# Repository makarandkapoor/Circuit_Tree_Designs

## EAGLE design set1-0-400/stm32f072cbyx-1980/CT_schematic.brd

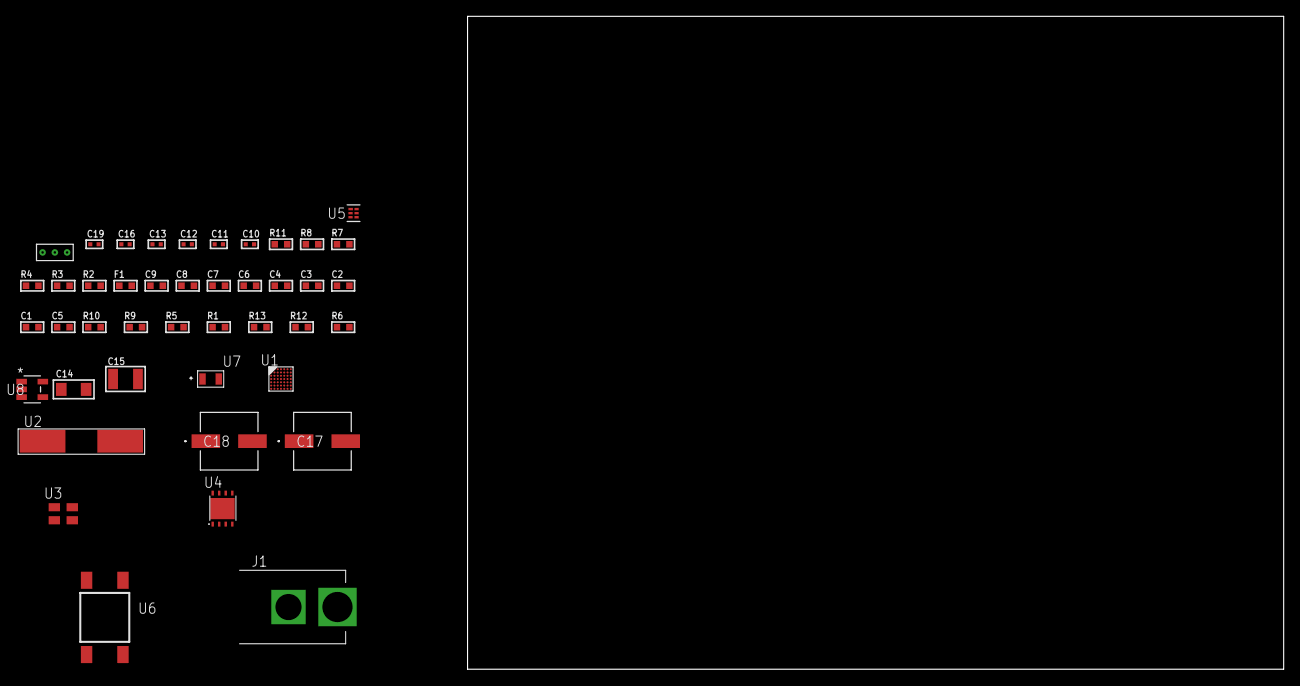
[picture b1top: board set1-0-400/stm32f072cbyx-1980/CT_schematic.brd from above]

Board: 2 copper layers, 100.0 x 80.0 mm, 43 parts (0 on the bottom side), 20 nets, no tracks yet.

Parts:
C1, C9: 1e-06; C0603
C2, C3, C4, C6, C7: 1e-07; C0603
C5: 4.7e-06; C0603
C8: 1e-08; C0603
C10, C11: 1e-11; C0402
C12, C13, C19: 1e-08; C0402
C14: 1e-05; C1206
C15: 1e-05; C1210
C16: 1e-07; C0402
C17, C18: 0.0001; EXV-9H
F1: 240.0; L0603
J1: PJ-037B; PJ-037B_PACKAGE
R1, R5, R9, R10: 10000.0; R0603
R2, R8: 1000.0; R0603
R3: 1600.5; R0603
R4: 4700.0; R0603
R6: 100000.0; R0603
R7: 2231.0; R0603
R11: 9100.0; R0603
R12: 680000.0; R0603
R13: 120000.0; R0603
U1: stm32f072cby6; WLCSP49
U2: ABLS-25.000MHZ-B2F-T
U3: ASEK-32.768KHz-ECST; ASEK
U4: LP3878SDX-ADJ/NOPB; WSON-8
U5: TPS3895ADRYR; SON-6
U6: 4-1437565-2; SW_4-1437565-2
U7: Q65110A2395; LGM67K-G1J2-24-Z
U8: nc7sz125m5x; NC7SZ125M5X
U9: Dummy; DUMMY_PACKAGE_86

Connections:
CLK_CRYSTAL_U1_D6: C10.1, U1.D6, U2.1
CLK_CRYSTAL_U1_D7: C11.1, U1.D7, U2.2
CLK_U1_C7: U1.C7, U3.3
GND: C1.2, C2.2, C3.2, C4.2, C5.2, C6.2, C7.2, C8.2, C9.2, C10.2, C11.2, C12.2, C13.2, C14.2, C15.2, C16.2, C17.2, C18.2, C19.2, J1.2, R2.2, R5.2, R8.2, R11.2, R13.2, U1.A6, U1.B1, U1.D3, U1.E6, U3.2, U4.3, U4.PAD, U5.2, U7.C, U8.1, U8.3, U9.1
NET_U1_A5: R5.1, U1.A5
NET_U1_E7: R4.1, U1.E7, U8.4
NET_U1_F7: C8.1, C9.1, F1.1, U1.F7
NET_U1_G6: R3.1, U1.G6, U7.A
NET_U1_G7: R1.1, U1.G7, U6.3, U6.4
NET_U4_1: C13.1, U4.1
NET_U4_6: R7.2, R8.1, U4.6
NET_U4_8: R6.1, U4.8
NET_U5_1: R10.1, R11.1, U5.1
NET_U5_3: R12.2, R13.1, U5.3
NET_U5_4: R9.1, U5.4, U8.2
NET_U6_1: R2.1, U6.1, U6.2
PROC_TIM1_CH2: U1.D2, U9.2
PROC_TIM1_CH4: U1.C1, U9.3
VCC_S1_8V5: C14.1, C17.1, C18.1, J1.1, R6.2, U4.4
VCC_TIER1_3V3: C1.1, C2.1, C3.1, C4.1, C5.1, C6.1, C7.1, C12.1, C15.1, C16.1, C19.1, F1.2, R1.2, R3.2, R4.2, R7.1, R9.2, R10.2, R12.1, U1.A7, U1.B2, U1.B7, U1.F2, U3.4, U4.5, U5.6, U8.5

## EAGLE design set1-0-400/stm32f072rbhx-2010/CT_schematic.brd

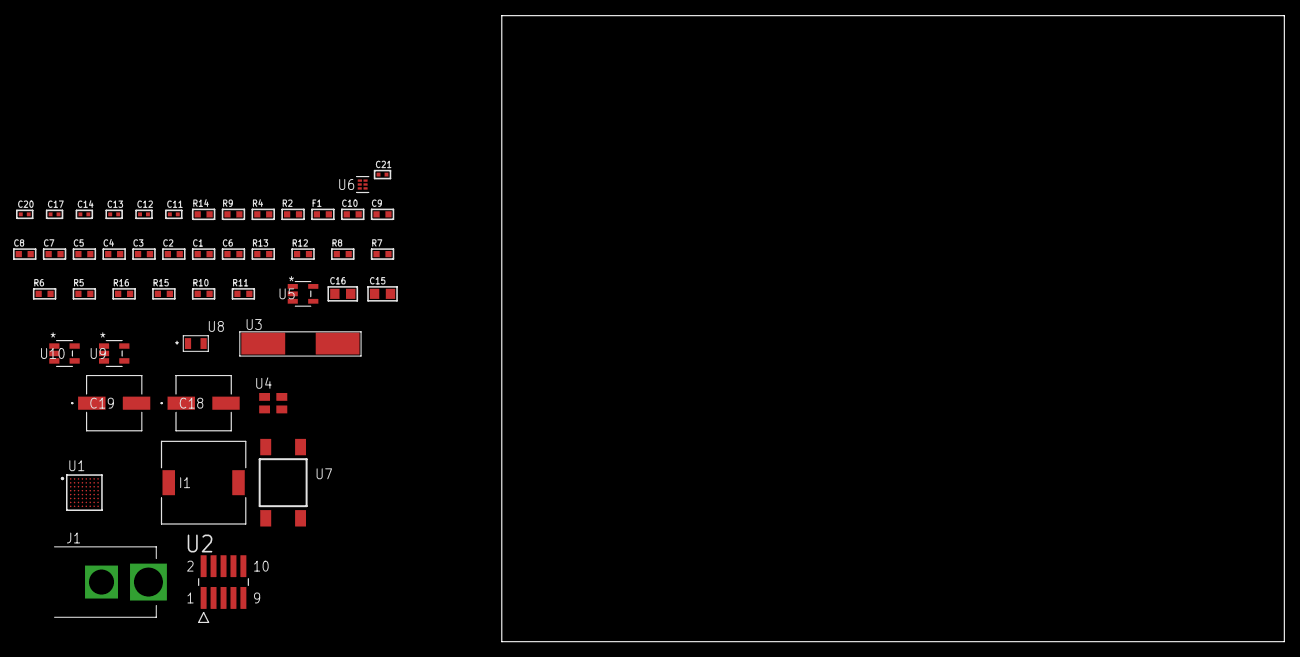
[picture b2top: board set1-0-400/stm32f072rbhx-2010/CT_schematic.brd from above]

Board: 2 copper layers, 100.0 x 80.0 mm, 48 parts (0 on the bottom side), 21 nets, no tracks yet.

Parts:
C1, C10: 1e-06; C0603
C2, C3, C4, C5, C7, C8: 1e-07; C0603
C6: 4.7e-06; C0603
C9: 1e-08; C0603
C11, C12: 1e-11; C0402
C13, C17: 1e-07; C0402
C14, C20, C21: 1e-08; C0402
C15, C16: 1e-05; C0805
C18, C19: 0.0001; EXV-9H
F1: 240.0; L0603
I1: 7e-06; DR1040
J1: PJ-037B; PJ-037B_PACKAGE
R2: 1000.0; R0603
R4: 4700.0; R0603
R5, R6, R7, R8, R12, R13: 10000.0; R0603
R9: 5.0; R0603
R10: 220000.0; R0603
R11: 1000000.0; R0603
R14: 9100.0; R0603
R15: 680000.0; R0603
R16: 120000.0; R0603
U1: stm32f072rbh7; UFBGA64
U2: FTSH-105-01-L-DV-K; SAMTEC_FTSH-105-01-L-DV-K
U3: ABLS-25.000MHZ-B2F-T
U4: ASEK-32.768KHz-ECST; ASEK
U5: ltc3406es5; TSOT-23-5
U6: TPS3895ADRYR; SON-6
U7: 4-1437565-2; SW_4-1437565-2
U8: Q65110A2395; LGM67K-G1J2-24-Z
U9, U10: nc7sz125m5x; NC7SZ125M5X

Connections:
CLK_CRYSTAL_U1_C1: C11.1, U1.C1, U3.1
CLK_CRYSTAL_U1_D1: C12.1, U1.D1, U3.2
CLK_U1_A1: U1.A1, U4.3
GND: C1.2, C2.2, C3.2, C4.2, C5.2, C6.2, C7.2, C8.2, C9.2, C10.2, C11.2, C12.2, C13.2, C14.2, C15.2, C16.1, C16.2, C17.2, C18.2, C19.2, C20.2, C21.2, J1.2, R2.2, R5.2, R9.2, R10.2, R14.2, R16.2, U1.C2, U1.D4, U1.D5, U1.D6, U1.F1, U2.3, U2.5, U4.2, U5.2, U6.2, U8.C, U9.2, U9.3, U10.1, U10.3
NET_U1_B4: R5.1, U1.B4
NET_U1_E1: R4.1, U1.E1, U10.4
NET_U1_H1: C9.1, C10.1, F1.1, U1.H1
NET_U1_H8: U7.3, U7.4
NET_U2_9: R9.1, U2.9
NET_U5_3: I1.1, U5.3
NET_U5_5: R10.1, R11.1, U5.5
NET_U5_ATNET_3: I1.2, R11.2
NET_U6_1: R13.1, R14.1, U6.1
NET_U6_3: R15.2, R16.1, U6.3
NET_U6_4: R12.1, U6.4, U9.4, U10.2
NET_U7_1: R2.1, U7.1, U7.2
PROC_SYS_SWCLK: R7.1, U1.A7, U2.4
PROC_SYS_SWDIO: R8.1, U1.A8, U2.2
RST_OUT_U2_JTAG_RST_B: R6.1, U2.10, U9.1
VCC_S1_4V8: C15.1, C18.1, C19.1, J1.1, U5.4
VCC_TIER1_3V3: C1.1, C2.1, C3.1, C4.1, C5.1, C6.1, C7.1, C8.1, C13.1, C14.1, C16.2, C17.1, C20.1, C21.1, F1.2, I1.2, R4.2, R6.2, R7.2, R8.2, R11.2, R12.2, R13.2, R15.1, U1.B2, U1.D2, U1.E4, U1.E5, U1.E6, U2.1, U4.4, U6.6, U9.5, U10.5

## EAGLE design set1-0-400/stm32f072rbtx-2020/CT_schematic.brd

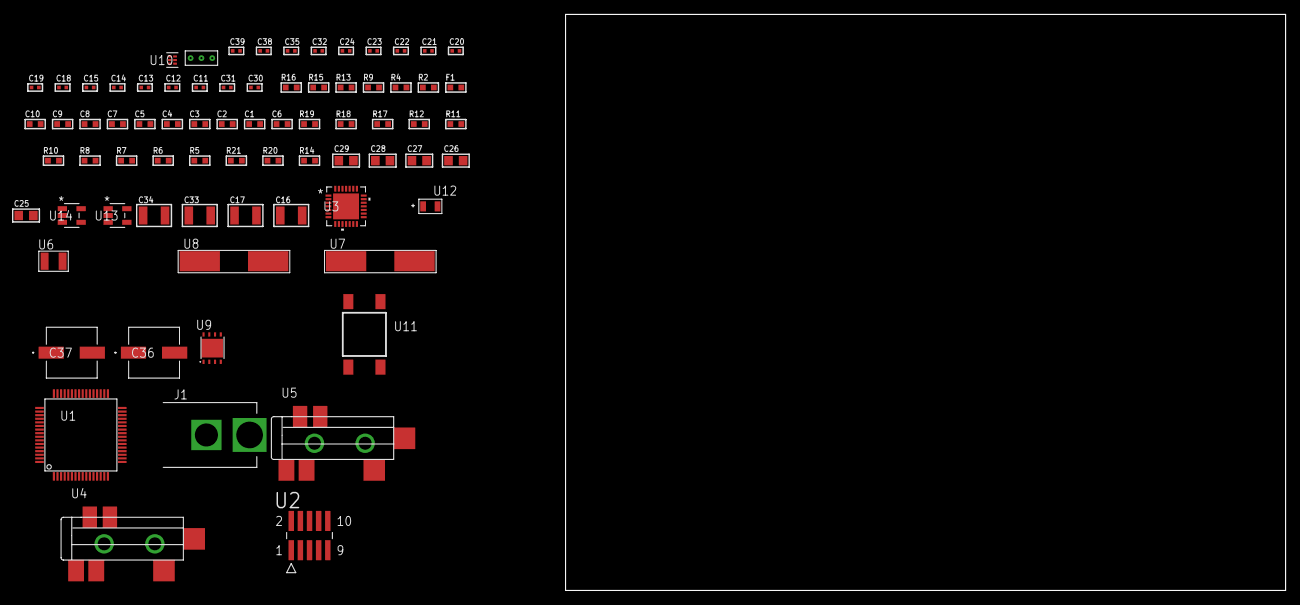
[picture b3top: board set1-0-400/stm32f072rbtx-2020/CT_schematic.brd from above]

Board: 2 copper layers, 100.0 x 80.0 mm, 75 parts (0 on the bottom side), 33 nets, no tracks yet.

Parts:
C1, C10: 1e-06; C0603
C2, C3, C4, C5, C7, C8: 1e-07; C0603
C6: 4.7e-06; C0603
C9: 1e-08; C0603
C11, C12, C13, C14: 1e-11; C0402
C15, C20, C21, C22, C23, C24, C35: 1e-07; C0402
C16, C17: 2.2e-05; C1210
C18, C19: 1e-09; C0402
C25, C26, C27, C28, C29: 1e-05; C0805
C30, C31: 2.2e-11; C0402
C32, C38, C39: 1e-08; C0402
C33, C34: 1e-05; C1210
C36, C37: 0.0001; EXV-9H
F1: 240.0; L0603
J1: PJ-037B; PJ-037B_PACKAGE
R2, R16: 1000.0; R0603
R4: 4700.0; R0603
R5, R6, R7, R8, R17, R18: 10000.0; R0603
R9: 5.0; R0603
R10, R11, R12: 47000.0; R0603
R13: 680.0; R0603
R14: 100000.0; R0603
R15: 1500.0; R0603
R19: 18000.0; R0603
R20: 470000.0; R0603
R21: 120000.0; R0603
U1: stm32f072rbt7; LQFP64
U2: FTSH-105-01-L-DV-K; SAMTEC_FTSH-105-01-L-DV-K
U3: WM8731CLSEFL; QFN-28
U4, U5: SJ-43515TS-SMT-TR
U6: ABS07-32.768KHZ-7-T
U7: ABLS-25.000MHZ-B2F-T
U8: ABLS-12.288MHZ-B4-T
U9: LP3878SDX-ADJ/NOPB; WSON-8
U10: TPS3895ADRYR; SON-6
U11: 4-1437565-2; SW_4-1437565-2
U12: Q65110A2395; LGM67K-G1J2-24-Z
U13, U14: nc7sz125m5x; NC7SZ125M5X
U15: Dummy; DUMMY_PACKAGE_153

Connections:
CLK_CRYSTAL_U1_3: C11.1, U1.3, U6.1
CLK_CRYSTAL_U1_4: C12.1, U1.4, U6.2
CLK_CRYSTAL_U1_5: C13.1, U1.5, U7.1
CLK_CRYSTAL_U1_6: C14.1, U1.6, U7.2
CLK_CRYSTAL_U3_1: C30.1, U3.1, U8.1
CLK_CRYSTAL_U3_2: C31.1, U3.2, U8.2
GND: C1.2, C2.2, C3.2, C4.2, C5.2, C6.2, C7.2, C8.2, C9.2, C10.2, C11.2, C12.2, C13.2, C14.2, C15.2, C19.2, C20.2, C21.2, C22.2, C23.2, C24.2, C25.2, C26.2, C27.2, C28.2, C29.2, C30.2, C31.2, C32.2, C33.2, C34.2, C35.2, C36.2, C37.2, C38.2, C39.2, J1.2, R2.2, R5.2, R9.2, R10.2, R11.2, R12.2, R16.2, R19.2, R21.2, U1.12, U1.18, U1.31, U1.47, U1.63, U2.3, U2.5, U3.4, U3.15, U3.19, U3.25, U3.26, U3.29, U4.1, U5.1, U9.3, U9.PAD, U10.2, U12.C, U13.2, U13.3, U14.1, U14.3, U15.1
NET_U1_7: R4.1, U1.7, U14.4
NET_U1_13: C9.1, C10.1, F1.1, U1.13
NET_U1_60: R5.1, U1.60
NET_U1_62: U11.3, U11.4
NET_U2_9: R9.1, U2.9
NET_U3_20: C24.1, C29.1, U3.20
NET_U4_2: C17.1, R11.1, U4.2
NET_U4_5: C16.1, R10.1, U4.5
NET_U5_5: C18.1, C19.1, R12.1, R13.1, U5.5
NET_U9_1: C32.1, U9.1
NET_U9_6: R15.2, R16.1, U9.6
NET_U9_8: R14.1, U9.8
NET_U10_1: R18.1, R19.1, U10.1
NET_U10_3: R20.2, R21.1, U10.3
NET_U10_4: R17.1, U10.4, U13.4, U14.2
NET_U11_1: R2.1, U11.1, U11.2
PROC_ADC_IN3: U1.17, U15.3
PROC_ADC_IN13: U1.11, U15.2
PROC_I2S1_CK: U1.21, U3.7
PROC_I2S1_SD: U1.23, U3.8
PROC_I2S1_WS: U1.20, U3.9, U3.11
PROC_SYS_SWCLK: R7.1, U1.49, U2.4
PROC_SYS_SWDIO: R8.1, U1.46, U2.2
RST_OUT_U2_JTAG_RST_B: R6.1, U2.10, U13.1
VCC_S1_13V4: C33.1, C36.1, C37.1, J1.1, R14.2, U9.4
VCC_TIER1_2V5: C1.1, C2.1, C3.1, C4.1, C5.1, C6.1, C7.1, C8.1, C15.1, C20.1, C21.1, C22.1, C23.1, C25.1, C26.1, C27.1, C28.1, C34.1, C35.1, C38.1, C39.1, F1.2, R4.2, R6.2, R7.2, R8.2, R15.1, R17.2, R18.2, R20.1, U1.1, U1.19, U1.32, U1.48, U1.64, U2.1, U3.3, U3.5, U3.12, U3.18, U9.5, U10.6, U13.5, U14.5

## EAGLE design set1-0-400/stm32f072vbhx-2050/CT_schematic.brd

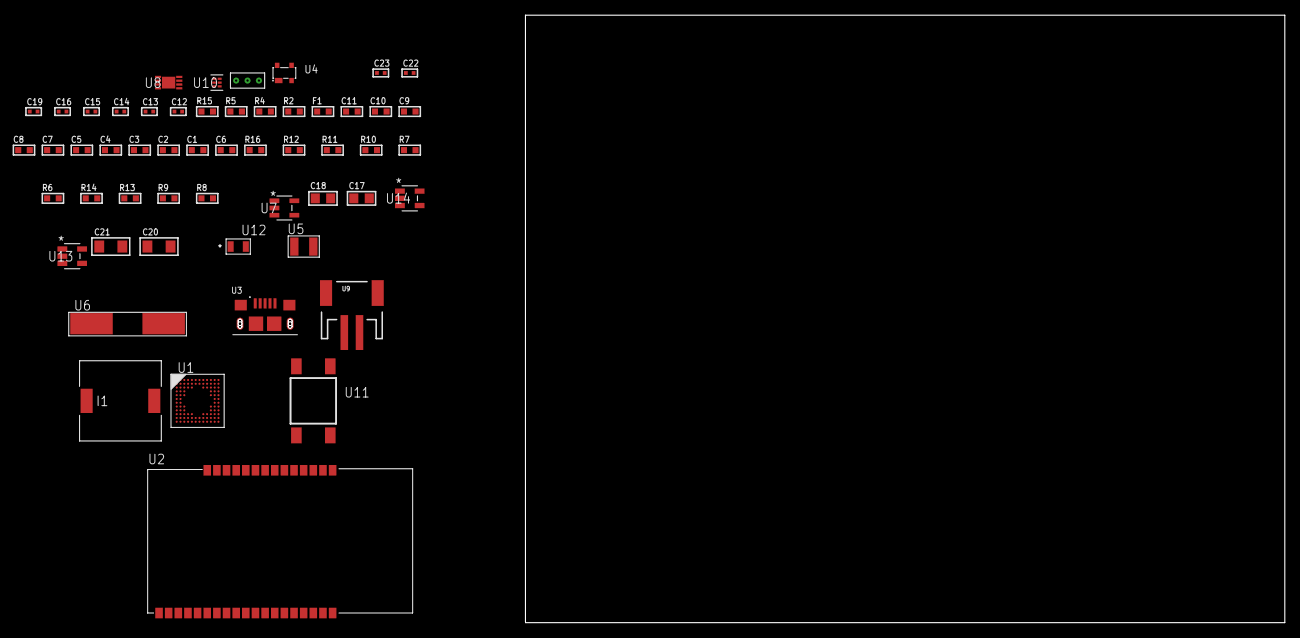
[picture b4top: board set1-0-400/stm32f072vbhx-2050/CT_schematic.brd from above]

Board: 2 copper layers, 54 parts (0 on the bottom side), 31 nets, no tracks yet.

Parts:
C1, C11: 1e-06; C0603
C2, C3, C4, C5, C7, C8, C9: 1e-07; C0603
C6: 4.7e-06; C0603
C10: 1e-08; C0603
C12, C13, C14, C15: 1e-11; C0402
C16, C19: 1e-07; C0402
C17, C18: 1e-05; C0805
C20, C21: 1e-05; C1206
C22, C23: 1e-08; C0402
F1: 240.0; L0603
I1: 3.8e-06; DR1040
R2: 1000.0; R0603
R4, R5: 4700.0; R0603
R6, R7, R10, R11, R16: 10000.0; R0603
R8: 309473.68421053; R0603
R9: 1000000.0; R0603
R12: 18000.0; R0603
R13: 470000.0; R0603
R14: 120000.0; R0603
R15: 2000.0; R0603
U1: stm32f072vbh7; UFBGA100
U2: ETRX3587
U3: 10118193-0001LF; FCI_10118193-0001LF
U4: prtr5v0u2ax; SOT143B
U5: ABS07-32.768KHZ-7-T
U6: ABLS-25.000MHZ-B2F-T
U7: ltc3406es5; TSOT-23-5
U8: MCP73831T-2ACI/MC; DFN8_2X3MC
U9: S2B-PH-SM4-TB(LF)(SN); JST-2-SMD
U10: TPS3895ADRYR; SON-6
U11: 4-1437565-2; SW_4-1437565-2
U12: Q65110A2395; LGM67K-G1J2-24-Z
U13, U14: nc7sz125m5x; NC7SZ125M5X
U15: Dummy; DUMMY_PACKAGE_117

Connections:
CLK_CRYSTAL_U1_D1: C12.1, U1.D1, U5.1
CLK_CRYSTAL_U1_E1: C13.1, U1.E1, U5.2
CLK_CRYSTAL_U1_F1: C14.1, U1.F1, U6.1
CLK_CRYSTAL_U1_G1: C15.1, U1.G1, U6.2
GND: C1.2, C2.2, C3.2, C4.2, C5.2, C6.2, C7.2, C8.2, C9.2, C10.2, C11.2, C12.2, C13.2, C14.2, C15.2, C16.2, C17.2, C18.1, C18.2, C19.2, C20.2, C21.2, C22.2, C23.2, R2.2, R6.2, R7.2, R8.2, R12.2, R14.2, R15.2, U1.D3, U1.F11, U1.F12, U1.K1, U2.1, U2.13, U2.19, U2.20, U2.31, U2.33, U3.5, U3.6, U3.7, U3.8, U3.9, U4.1, U7.2, U8.6, U8.9, U9.2, U10.2, U12.C, U13.1, U13.3, U14.1, U14.3, U15.1
INPUT_USBPOWER_5V: C20.1, R16.2, U3.1, U4.4, U8.1, U8.2
NET_U1_A4: R6.1, U1.A4
NET_U1_H2: R5.1, U1.H2, U14.4
NET_U1_M1: C10.1, C11.1, F1.1, U1.M1
NET_U1_M12: U11.3, U11.4
NET_U2_7: R4.1, U2.7, U13.4
NET_U2_21: R7.1, U2.21
NET_U7_3: I1.1, U7.3
NET_U7_5: R8.1, R9.1, U7.5
NET_U7_ATNET_3: I1.2, R9.2
NET_U8_5: R16.1, U8.5
NET_U8_8: R15.1, U8.8
NET_U10_1: R11.1, R12.1, U10.1
NET_U10_3: R13.2, R14.1, U10.3
NET_U10_4: R10.1, U10.4, U13.2, U14.2
NET_U11_1: R2.1, U11.1, U11.2
PROC_PE1: U1.A2, U15.3
PROC_PE3: U1.A1, U15.2
PROC_USART2_CTS: U1.B8, U2.8
PROC_USART2_RTS: U1.B7, U2.6
PROC_USART2_RX: U1.A9, U2.17
PROC_USART2_TX: U1.A6, U2.18
PROC_USB_DM: U1.B12, U3.2, U4.3
PROC_USB_DP: U1.A12, U3.3, U4.2
VCC_S1_3V7: C17.1, C21.1, U7.4, U8.3, U8.4, U9.1
VCC_TIER1_2V5: C1.1, C2.1, C3.1, C4.1, C5.1, C6.1, C7.1, C8.1, C9.1, C16.1, C18.2, C19.1, C22.1, C23.1, F1.2, I1.2, R4.2, R5.2, R9.2, R10.2, R11.2, R13.1, U1.C4, U1.E2, U1.G11, U1.G12, U1.H3, U2.32, U10.6, U13.5, U14.5

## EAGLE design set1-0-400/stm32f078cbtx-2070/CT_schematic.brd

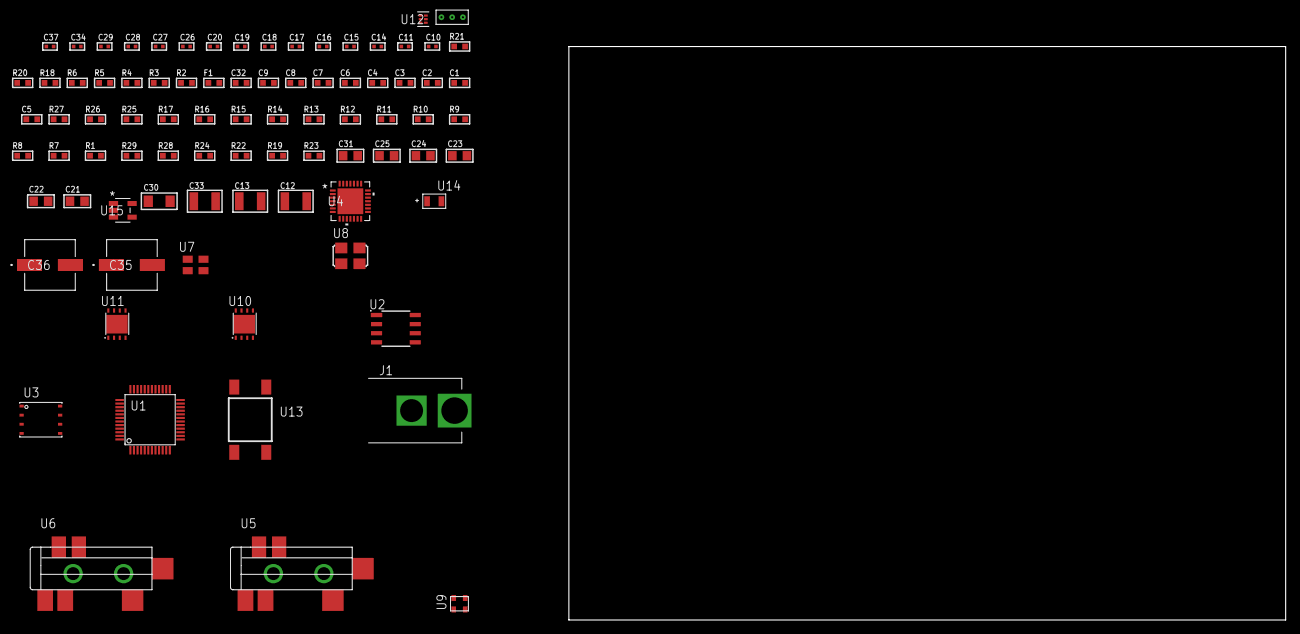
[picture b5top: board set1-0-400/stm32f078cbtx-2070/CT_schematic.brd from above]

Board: 2 copper layers, 100.0 x 80.0 mm, 84 parts (0 on the bottom side), 42 nets, no tracks yet.

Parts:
C1, C9, C32: 1e-06; C0603
C2, C3, C4, C6, C7: 1e-07; C0603
C5: 4.7e-06; C0603
C8: 1e-08; C0603
C10, C11, C26, C27, C28, C29, C37: 1e-08; C0402
C12, C13: 2.2e-05; C1210
C14, C15: 1e-09; C0402
C16, C17, C18, C19, C20, C34: 1e-07; C0402
C21, C22, C23, C24, C25, C31: 1e-05; C0805
C30: 1e-05; C1206
C33: 1e-05; C1210
C35, C36: 0.0001; EXV-9H
F1: 240.0; L0603
J1: PJ-037B; PJ-037B_PACKAGE
R1, R7, R8, R9, R10, R11, R12, R13, R14, R25, R26: 10000.0; R0603
R2, R21: 1000.0; R0603
R3: 910.0; R0603
R4: 4700.0; R0603
R5, R6: 2200.0; R0603
R15, R16, R17: 47000.0; R0603
R18: 680.0; R0603
R19, R22, R24: 100000.0; R0603
R20: 806.0; R0603
R23: 153694.38; R0603
R27: 82000.0; R0603
R28: 300000.0; R0603
R29: 120000.0; R0603
U1: stm32f078cbt7; LQFP48
U2: AT25010B-SSHL-T; SOIC-8
U3: 24AA512-I/MF; DFN8-S
U4: WM8731CLSEFL; QFN-28
U5, U6: SJ-43515TS-SMT-TR
U7: ASEK-2-32.768KHz-ECST; ASEK
U8: ASFL1-12.288MHZ-EC-T; ASFL1
U9: ASDMB-25.000MHZ-EC-T; ASDMB-XX.XXXXMHZ-XX-XX-XXX
U10: LP3878SDX-ADJ/NOPB; WSON-8
U11: LP2951ACSDX/NOPB; WSON-8
U12: TPS3895ADRYR; SON-6
U13: 4-1437565-2; SW_4-1437565-2
U14: Q65110A2395; LGM67K-G1J2-24-Z
U15: nc7sz125m5x; NC7SZ125M5X
U16: Dummy; DUMMY_PACKAGE_179

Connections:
CLK_U1_3: U1.3, U7.3
CLK_U1_5: U1.5, U9.3
CLK_U4_1: U4.1, U8.3
GND: C1.2, C2.2, C3.2, C4.2, C5.2, C6.2, C7.2, C8.2, C9.2, C10.2, C11.2, C15.2, C16.2, C17.2, C18.2, C19.2, C20.2, C21.2, C22.2, C23.2, C24.2, C25.2, C26.2, C27.2, C28.2, C29.2, C30.2, C31.2, C32.2, C33.2, C34.2, C35.2, C36.2, C37.2, J1.2, R2.2, R7.2, R8.2, R13.2, R14.2, R15.2, R16.2, R17.2, R21.2, R24.2, R27.2, R29.2, U1.8, U1.23, U1.35, U1.47, U2.4, U3.4, U3.7, U4.4, U4.15, U4.19, U4.25, U4.26, U4.29, U5.1, U6.1, U7.2, U8.2, U9.2, U10.3, U10.PAD, U11.3, U11.4, U11.PAD, U12.2, U14.C, U15.1, U15.3, U16.1
NET_U1_7: R4.1, U1.7, U15.4
NET_U1_9: C8.1, C9.1, F1.1, U1.9
NET_U1_20: R8.1, U1.20
NET_U1_42: R5.1, U1.42, U3.6
NET_U1_43: R6.1, U1.43, U3.5
NET_U1_44: R7.1, U1.44
NET_U1_45: R3.1, U1.45, U14.A
NET_U1_46: R1.1, U1.46, U13.3, U13.4
NET_U2_3: R9.1, U2.3
NET_U2_7: R11.1, U2.7
NET_U3_1: R12.1, U3.1
NET_U3_2: R13.1, U3.2
NET_U3_3: R14.1, U3.3
NET_U4_20: C20.1, C25.1, U4.20
NET_U5_2: C13.1, R16.1, U5.2
NET_U5_5: C12.1, R15.1, U5.5
NET_U6_5: C14.1, C15.1, R17.1, R18.1, U6.5
NET_U10_1: C29.1, U10.1
NET_U10_6: R20.2, R21.1, U10.6
NET_U10_8: R19.1, U10.8
NET_U11_5: R22.1, U11.5
NET_U11_7: R23.2, R24.1, U11.7
NET_U12_1: R26.1, R27.1, U12.1
NET_U12_3: R28.2, R29.1, U12.3
NET_U12_4: R25.1, U12.4, U15.2
NET_U13_1: R2.1, U13.1, U13.2
PROC_I2S1_CK: U1.39, U4.7
PROC_I2S1_SD: U1.41, U4.8
PROC_I2S1_WS: U1.38, U4.9, U4.11
PROC_SPI1_MISO: U1.16, U2.2
PROC_SPI1_MOSI: U1.17, U2.5
PROC_SPI1_NSS: R10.1, U1.14, U2.1
PROC_SPI1_SCK: U1.15, U2.6
PROC_TIM1_CH2: U1.30, U16.2
PROC_TIM1_CH4: U1.32, U16.3
VCC_S1_6V8: C30.1, C32.1, C35.1, C36.1, J1.1, R19.2, U10.4, U11.8
VCC_TIER1_1V8: C1.1, C2.1, C3.1, C4.1, C5.1, C6.1, C7.1, C10.1, C11.1, C16.1, C17.1, C18.1, C19.1, C21.1, C22.1, C23.1, C24.1, C26.1, C28.1, C31.1, C34.1, C37.1, F1.2, R1.2, R3.2, R4.2, R5.2, R6.2, R9.2, R10.2, R11.2, R12.2, R20.1, R25.2, R26.2, R28.1, U1.1, U1.24, U1.36, U1.48, U2.8, U3.8, U4.3, U4.5, U4.12, U4.18, U7.4, U9.4, U10.5, U12.6, U15.5
VCC_TIER1_3V3: C27.1, C33.1, R22.2, R23.1, U8.4, U11.1

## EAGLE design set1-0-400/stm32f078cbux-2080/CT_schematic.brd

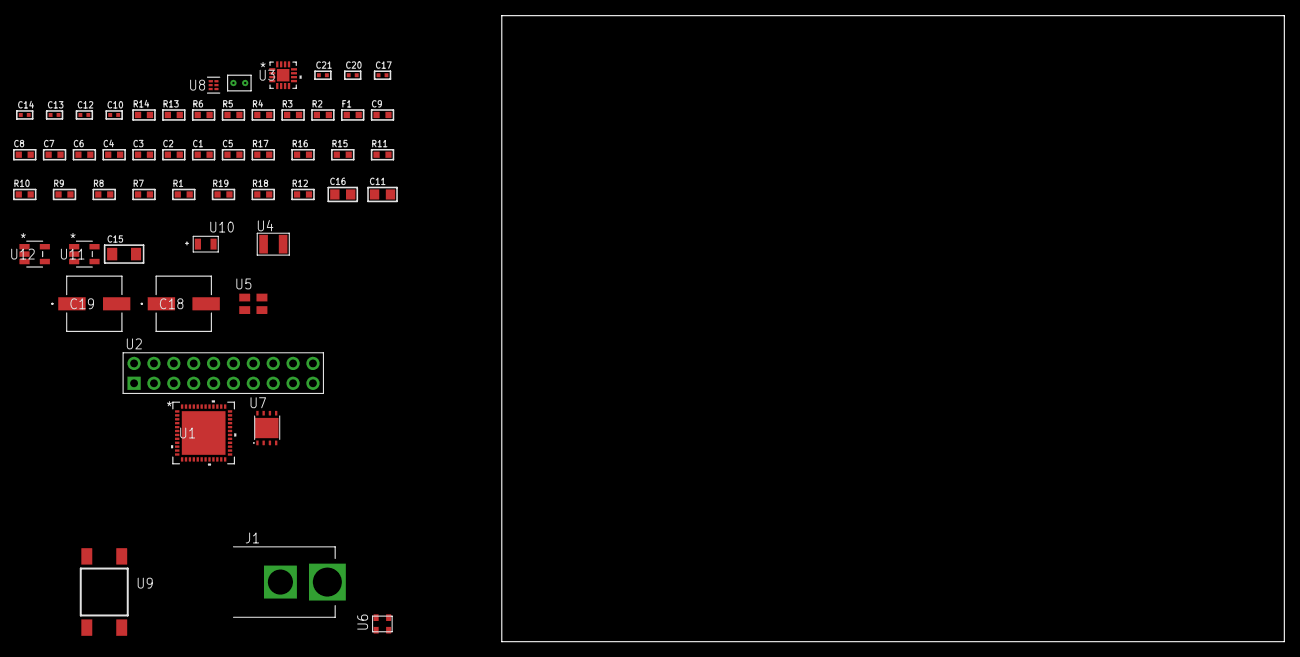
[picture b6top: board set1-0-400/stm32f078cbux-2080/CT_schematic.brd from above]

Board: 2 copper layers, 100.0 x 80.0 mm, 55 parts (0 on the bottom side), 28 nets, no tracks yet.

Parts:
C1, C9: 1e-06; C0603
C2, C3, C4, C6, C7: 1e-07; C0603
C5: 4.7e-06; C0603
C8: 1e-08; C0603
C10, C17: 1e-07; C0402
C11: 4.7e-06; C0805
C12, C13, C14, C20, C21: 1e-08; C0402
C15: 1e-05; C1206
C16: 1e-05; C0805
C18, C19: 0.0001; EXV-9H
F1: 240.0; L0603
J1: PJ-037B; PJ-037B_PACKAGE
R1, R7, R8, R9, R10, R11, R15, R16: 10000.0; R0603
R2, R14: 1000.0; R0603
R3: 910.0; R0603
R4: 4700.0; R0603
R5, R6: 2200.0; R0603
R12: 100000.0; R0603
R13: 806.0; R0603
R17: 82000.0; R0603
R18: 300000.0; R0603
R19: 120000.0; R0603
U1: stm32f078cbu7; UFQFPN48
U2: TST-110-05-T-D-RA
U3: M41T65Q6F; M41T65_QFN-16
U4: ABS07-32.768KHZ-7-T
U5: ASEK-2-32.768KHz-ECST; ASEK
U6: ASDMB-25.000MHZ-EC-T; ASDMB-XX.XXXXMHZ-XX-XX-XXX
U7: LP3878SDX-ADJ/NOPB; WSON-8
U8: TPS3895ADRYR; SON-6
U9: 4-1437565-2; SW_4-1437565-2
U10: Q65110A2395; LGM67K-G1J2-24-Z
U11, U12: nc7sz125m5x; NC7SZ125M5X
U13: Dummy; DUMMY_PACKAGE_115

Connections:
CLK_CRYSTAL_U3_1: U3.1, U4.1
CLK_CRYSTAL_U3_2: U3.2, U4.2
CLK_U1_3: U1.3, U5.3
CLK_U1_5: U1.5, U6.3
GND: C1.2, C2.2, C3.2, C4.2, C5.2, C6.2, C7.2, C8.2, C9.2, C10.2, C11.2, C12.2, C13.2, C14.2, C15.2, C16.2, C17.2, C18.2, C19.2, C20.2, C21.2, J1.2, R2.2, R7.2, R8.2, R14.2, R17.2, R19.2, U1.8, U1.23, U1.35, U1.47, U1.49, U2.4, U2.6, U2.8, U2.10, U2.12, U2.14, U2.16, U2.18, U2.20, U3.3, U3.5, U3.17, U5.2, U6.2, U7.3, U7.PAD, U8.2, U10.C, U11.2, U11.3, U12.1, U12.3, U13.1
NET_U1_7: R4.1, U1.7, U12.4
NET_U1_9: C8.1, C9.1, F1.1, U1.9
NET_U1_20: R8.1, U1.20
NET_U1_42: R5.1, U1.42, U3.10
NET_U1_43: R6.1, U1.43, U3.9
NET_U1_44: R7.1, U1.44
NET_U1_45: R3.1, U1.45, U10.A
NET_U1_46: R1.1, U1.46, U9.3, U9.4
NET_U3_4: R10.1, U3.4
NET_U3_11: R11.1, U3.11
NET_U7_1: C14.1, U7.1
NET_U7_6: R13.2, R14.1, U7.6
NET_U7_8: R12.1, U7.8
NET_U8_1: R16.1, R17.1, U8.1
NET_U8_3: R18.2, R19.1, U8.3
NET_U8_4: R15.1, U8.4, U11.4, U12.2
NET_U9_1: R2.1, U9.1, U9.2
PROC_DAC_OUT2: U1.15, U13.2
PROC_SYS_SWCLK: U1.37, U2.9
PROC_SYS_SWDIO: U1.34, U2.7
RST_OUT_U2_SRESET_B: R9.1, U2.15, U11.1
VCC_S1_11V0: C15.1, C18.1, C19.1, J1.1, R12.2, U7.4
VCC_TIER1_1V8: C1.1, C2.1, C3.1, C4.1, C5.1, C6.1, C7.1, C10.1, C11.1, C12.1, C13.1, C16.1, C17.1, C20.1, C21.1, F1.2, R1.2, R3.2, R4.2, R5.2, R6.2, R9.2, R10.2, R11.2, R13.1, R15.2, R16.2, R18.1, U1.1, U1.24, U1.36, U1.48, U2.1, U3.14, U5.4, U6.4, U7.5, U8.6, U11.5, U12.5

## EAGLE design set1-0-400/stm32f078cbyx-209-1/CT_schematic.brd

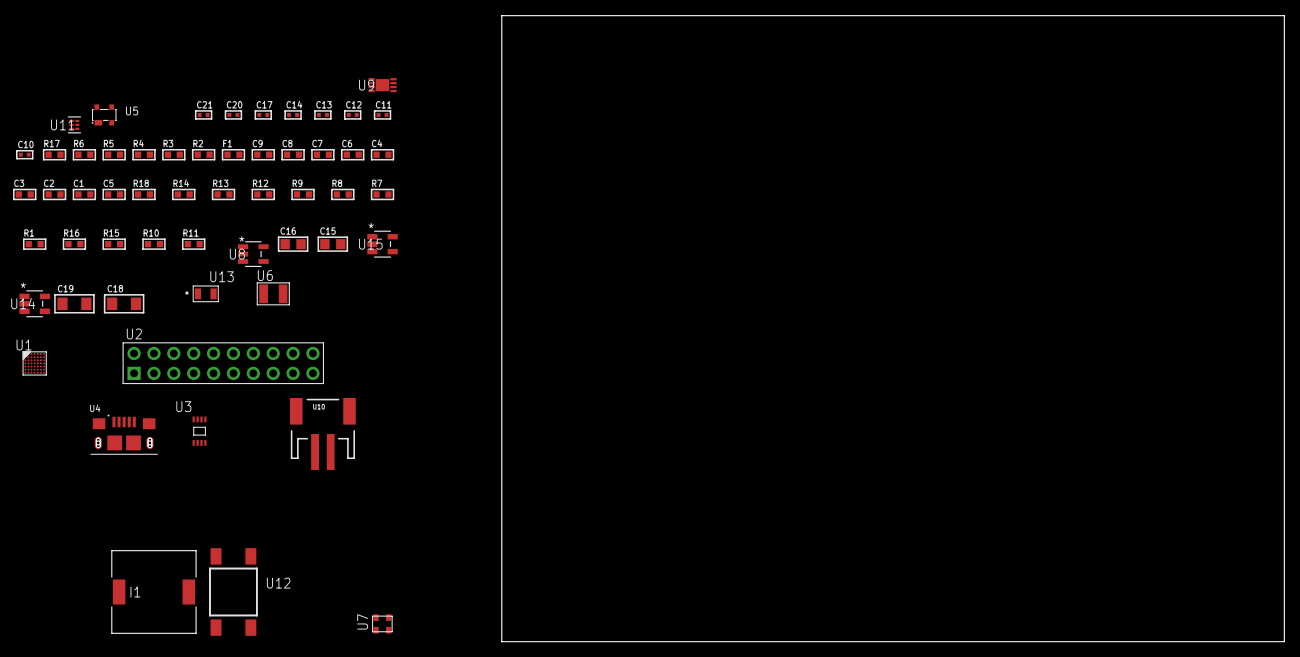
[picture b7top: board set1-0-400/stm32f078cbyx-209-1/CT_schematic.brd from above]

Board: 2 copper layers, 56 parts (0 on the bottom side), 29 nets, no tracks yet.

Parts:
C1, C9: 1e-06; C0603
C2, C3, C4, C6, C7: 1e-07; C0603
C5: 4.7e-06; C0603
C8: 1e-08; C0603
C10, C11: 1e-11; C0402
C12, C17: 1e-07; C0402
C13, C14, C20, C21: 1e-08; C0402
C15, C16: 1e-05; C0805
C18, C19: 1e-05; C1206
F1: 240.0; L0603
I1: 5.2e-06; DR1040
R1, R7, R8, R9, R12, R13, R18: 10000.0; R0603
R2: 1000.0; R0603
R3: 910.0; R0603
R4: 4700.0; R0603
R5, R6: 2200.0; R0603
R10: 490000.0; R0603
R11: 1000000.0; R0603
R14: 82000.0; R0603
R15: 300000.0; R0603
R16: 120000.0; R0603
R17: 2000.0; R0603
U1: stm32f078cby6; WLCSP49
U2: TST-110-05-T-D-RA
U3: 24AA01T-I/MNY; TDFN-8/6MM
U4: 10118193-0001LF; FCI_10118193-0001LF
U5: prtr5v0u2ax; SOT143B
U6: ABS07-32.768KHZ-7-T
U7: ASDMB-25.000MHZ-EC-T; ASDMB-XX.XXXXMHZ-XX-XX-XXX
U8: ltc3406es5; TSOT-23-5
U9: MCP73831T-2ACI/MC; DFN8_2X3MC
U10: S2B-PH-SM4-TB(LF)(SN); JST-2-SMD
U11: TPS3895ADRYR; SON-6
U12: 4-1437565-2; SW_4-1437565-2
U13: Q65110A2395; LGM67K-G1J2-24-Z
U14, U15: nc7sz125m5x; NC7SZ125M5X

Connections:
CLK_CRYSTAL_U1_C6: C10.1, U1.C6, U6.1
CLK_CRYSTAL_U1_C7: C11.1, U1.C7, U6.2
CLK_U1_D7: U1.D7, U7.3
GND: C1.2, C2.2, C3.2, C4.2, C5.2, C6.2, C7.2, C8.2, C9.2, C10.2, C11.2, C12.2, C13.2, C14.2, C15.2, C16.1, C16.2, C17.2, C18.2, C19.2, C20.2, C21.2, R2.2, R7.2, R8.2, R10.2, R14.2, R16.2, R17.2, U1.A6, U1.B1, U1.D3, U1.E6, U2.4, U2.6, U2.8, U2.10, U2.12, U2.14, U2.16, U2.18, U2.20, U3.4, U3.7, U4.5, U4.6, U4.7, U4.8, U4.9, U5.1, U7.2, U8.2, U9.6, U9.9, U10.2, U11.2, U13.C, U14.2, U14.3, U15.1, U15.3
INPUT_USBPOWER_5V: C18.1, R18.2, U4.1, U5.4, U9.1, U9.2
NET_U1_A5: R7.1, U1.A5
NET_U1_B5: R5.1, U1.B5, U3.6
NET_U1_C5: R6.1, U1.C5, U3.5
NET_U1_E7: R4.1, U1.E7, U15.4
NET_U1_F7: C8.1, C9.1, F1.1, U1.F7
NET_U1_G3: R8.1, U1.G3
NET_U1_G6: R3.1, U1.G6, U13.A
NET_U1_G7: R1.1, U1.G7, U12.3, U12.4
NET_U8_3: I1.1, U8.3
NET_U8_5: R10.1, R11.1, U8.5
NET_U8_ATNET_3: I1.2, R11.2
NET_U9_5: R18.1, U9.5
NET_U9_8: R17.1, U9.8
NET_U11_1: R13.1, R14.1, U11.1
NET_U11_3: R15.2, R16.1, U11.3
NET_U11_4: R12.1, U11.4, U14.4, U15.2
NET_U12_1: R2.1, U12.1, U12.2
PROC_SYS_SWCLK: U1.A1, U2.9
PROC_SYS_SWDIO: U1.B3, U2.7
PROC_USB_DM: U1.C1, U4.2, U5.3
PROC_USB_DP: U1.C3, U4.3, U5.2
RST_OUT_U2_SRESET_B: R9.1, U2.15, U14.1
VCC_S1_3V7: C15.1, C19.1, U8.4, U9.3, U9.4, U10.1
VCC_TIER1_1V8: C1.1, C2.1, C3.1, C4.1, C5.1, C6.1, C7.1, C12.1, C13.1, C14.1, C16.2, C17.1, C20.1, C21.1, F1.2, I1.2, R1.2, R3.2, R4.2, R5.2, R6.2, R9.2, R11.2, R12.2, R13.2, R15.1, U1.A7, U1.B2, U1.B7, U1.F2, U2.1, U3.8, U7.4, U11.6, U14.5, U15.5

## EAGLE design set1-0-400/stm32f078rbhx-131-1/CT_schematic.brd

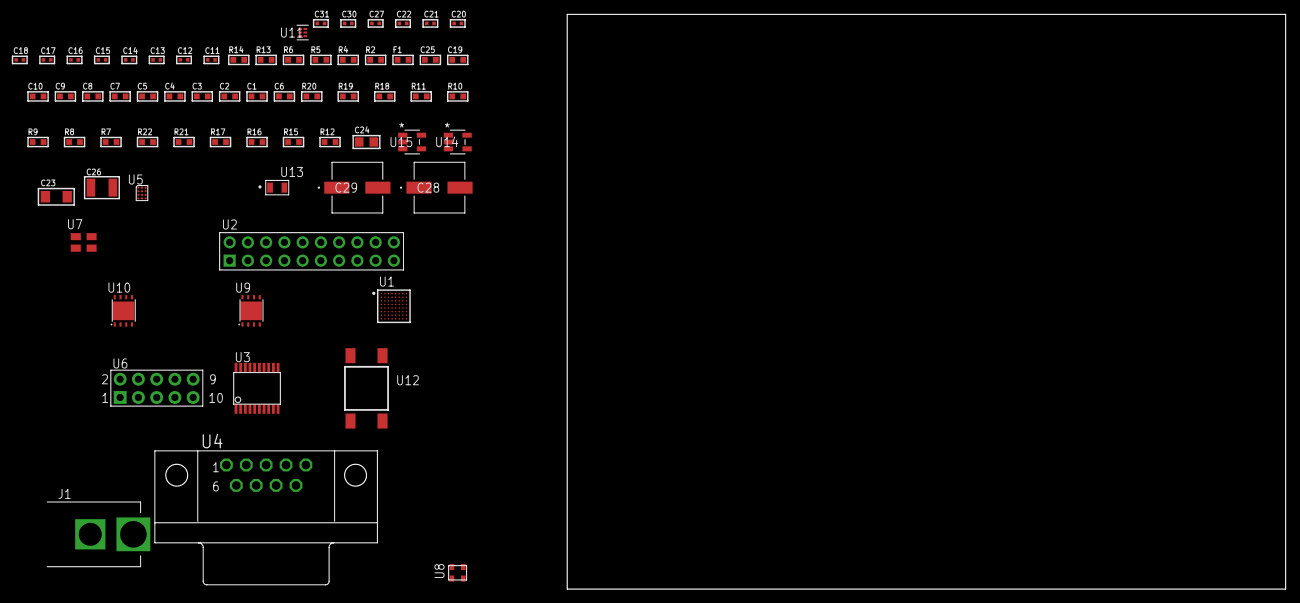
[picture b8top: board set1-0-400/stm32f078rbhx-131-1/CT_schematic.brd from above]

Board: 2 copper layers, 100.0 x 80.0 mm, 68 parts (0 on the bottom side), 45 nets, no tracks yet.

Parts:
C1, C10, C19, C25: 1e-06; C0603
C2, C3, C4, C5, C7, C8: 1e-07; C0603
C6: 4.7e-06; C0603
C9: 1e-08; C0603
C11, C12, C13, C14, C15, C16, C17, C18, C27: 1e-07; C0402
C20, C21, C22, C30, C31: 1e-08; C0402
C23: 1e-05; C1206
C24: 1e-05; C0805
C26: 1e-05; C1210
C28, C29: 0.0001; EXV-9H
F1: 240.0; L0603
J1: PJ-037B; PJ-037B_PACKAGE
R2, R14: 1000.0; R0603
R4: 4700.0; R0603
R5, R6: 2200.0; R0603
R7, R8, R9, R10, R11, R18, R19: 10000.0; R0603
R12, R15, R17: 100000.0; R0603
R13: 806.0; R0603
R16: 110000.0; R0603
R20: 82000.0; R0603
R21: 300000.0; R0603
R22: 120000.0; R0603
U1: STM32F078RBH6; UFBGA64
U2: TST-110-05-T-D-RA
U3: SP3203ECY-L/TR; TSSOP20-I
U4: 182-009-113R531; 182-009-MALE
U5: TSC2014IYZGT
U6: HTSS-105-01-G-D
U7: ASEK-2-32.768KHz-ECST; ASEK
U8: ASDMB-25.000MHZ-EC-T; ASDMB-XX.XXXXMHZ-XX-XX-XXX
U9: LP3878SDX-ADJ/NOPB; WSON-8
U10: LP2951ACSDX/NOPB; WSON-8
U11: TPS3895ADRYR; SON-6
U12: 4-1437565-2; SW_4-1437565-2
U13: Q65110A2395; LGM67K-G1J2-24-Z
U14, U15: nc7sz125m5x; NC7SZ125M5X

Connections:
CLK_U1_A1: U1.A1, U7.3
CLK_U1_C1: U1.C1, U8.3
GND: C1.2, C2.2, C3.2, C4.2, C5.2, C6.2, C7.2, C8.2, C9.2, C10.2, C11.2, C12.2, C13.2, C16.2, C17.2, C18.2, C19.2, C20.2, C21.2, C22.2, C23.2, C24.2, C25.2, C26.2, C27.2, C28.2, C29.2, C30.2, C31.2, J1.2, R2.2, R7.2, R8.2, R14.2, R17.2, R20.2, R22.2, U1.C2, U1.D4, U1.D5, U1.D6, U1.F1, U2.4, U2.6, U2.8, U2.10, U2.12, U2.14, U2.16, U2.18, U2.20, U3.18, U4.5, U5.D2, U6.9, U7.2, U8.2, U9.3, U9.PAD, U10.3, U10.4, U10.PAD, U11.2, U13.C, U14.2, U14.3, U15.1, U15.3
NET_U1_A3: R6.1, U1.A3, U5.C1
NET_U1_B3: R5.1, U1.B3, U5.D1
NET_U1_B4: R7.1, U1.B4
NET_U1_E1: R4.1, U1.E1, U15.4
NET_U1_G6: R8.1, U1.G6
NET_U1_H1: C9.1, C10.1, F1.1, U1.H1
NET_U1_H8: U12.3, U12.4
NET_U3_1: C14.1, U3.1
NET_U3_2: C16.1, U3.2
NET_U3_3: C14.2, U3.3
NET_U3_4: C15.1, U3.4
NET_U3_5: C15.2, U3.5
NET_U3_6: C17.1, U3.6
NET_U4_2: U3.14, U4.2
NET_U4_3: U3.17, U4.3
NET_U4_7: U3.13, U4.7
NET_U4_8: U3.16, U4.8
NET_U5_B1: R11.1, U5.B1
NET_U5_C2: R10.1, U5.C2
NET_U6_3: U5.B3, U6.3
NET_U6_4: U5.D3, U6.4
NET_U6_5: U5.A3, U6.5
NET_U6_6: U5.C3, U6.6
NET_U9_1: C22.1, U9.1
NET_U9_6: R13.2, R14.1, U9.6
NET_U9_8: R12.1, U9.8
NET_U10_5: R15.1, U10.5
NET_U10_7: R16.2, R17.1, U10.7
NET_U11_1: R19.1, R20.1, U11.1
NET_U11_3: R21.2, R22.1, U11.3
NET_U11_4: R18.1, U11.4, U14.4, U15.2
NET_U12_1: R2.1, U12.1, U12.2
PROC_SYS_SWCLK: U1.A7, U2.9
PROC_SYS_SWDIO: U1.A8, U2.7
PROC_USART1_CTS: U1.C8, U3.8
PROC_USART1_RTS: U1.B8, U3.10
PROC_USART1_RX: U1.C3, U3.11
PROC_USART1_TX: U1.C7, U3.7
RST_OUT_U2_SRESET_B: R9.1, U2.15, U14.1
VCC_S1_6V1: C23.1, C25.1, C28.1, C29.1, J1.1, R12.2, U9.4, U10.8
VCC_TIER1_1V8: C1.1, C2.1, C3.1, C4.1, C5.1, C6.1, C7.1, C8.1, C11.1, C13.1, C18.1, C19.1, C20.1, C21.1, C24.1, C27.1, C30.1, C31.1, F1.2, R4.2, R5.2, R6.2, R9.2, R10.2, R11.2, R13.1, R18.2, R19.2, R21.1, U1.B2, U1.D2, U1.E4, U1.E5, U1.E6, U2.1, U3.12, U5.A2, U5.B2, U7.4, U8.4, U9.5, U11.6, U14.5, U15.5
VCC_TIER1_2V7: C12.1, C26.1, R15.2, R16.1, U3.19, U10.1

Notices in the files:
parts and their libraries:
circuit_tree: (C) 2014 Tomasz Boleslaw CEDRO, cederom@tlen.pl, http://www.tomek.cedro.info.
